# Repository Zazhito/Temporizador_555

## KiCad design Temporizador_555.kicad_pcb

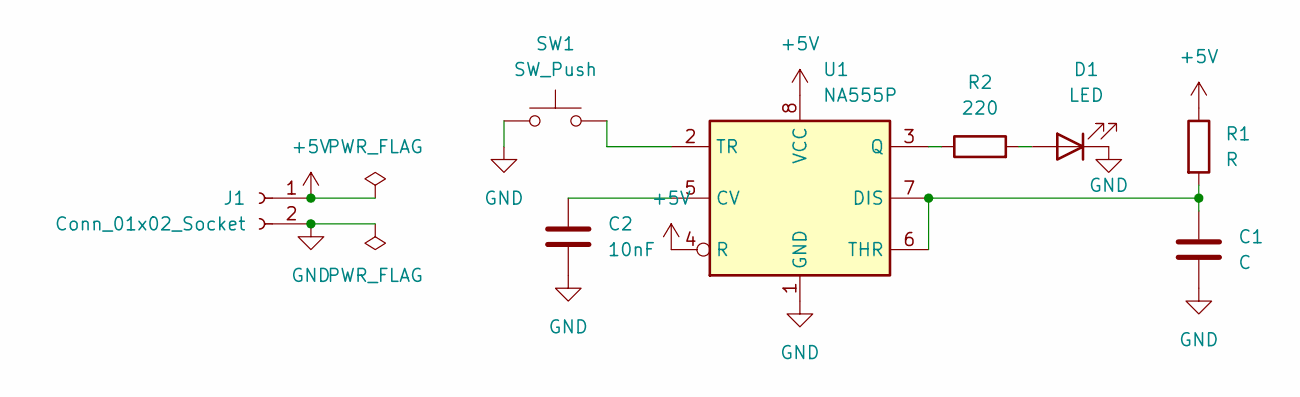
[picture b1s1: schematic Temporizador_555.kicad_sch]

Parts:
C1: C; CP_Radial_D5.0mm_P2.00mm
C2: 10nF; C_Disc_D5.0mm_W2.5mm_P5.00mm
D1: LED; LED_D3.0mm
J1: Conn_01x02_Socket; PinSocket_1x02_P2.54mm_Vertical
R1: R; R_Axial_DIN0207_L6.3mm_D2.5mm_P7.62mm_Horizontal
R2: 220; R_Axial_DIN0207_L6.3mm_D2.5mm_P7.62mm_Horizontal
SW1: SW_Push; SW_PUSH_6mm
U1: NA555P; DIP-8_W7.62mm

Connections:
+5V: J1.1, R1.1, U1.4 (R), U1.8 (VCC)
GND: C1.2, C2.2, D1.1 (K), J1.2, SW1.1, U1.1 (GND)
unnamed: D1.2 (A), R2.2
unnamed: C2.1, U1.5 (CV)
unnamed: C1.1, R1.2, U1.6 (THR), U1.7 (DIS)
unnamed: R2.1, U1.3 (Q)
unnamed: SW1.2, U1.2 (TR)

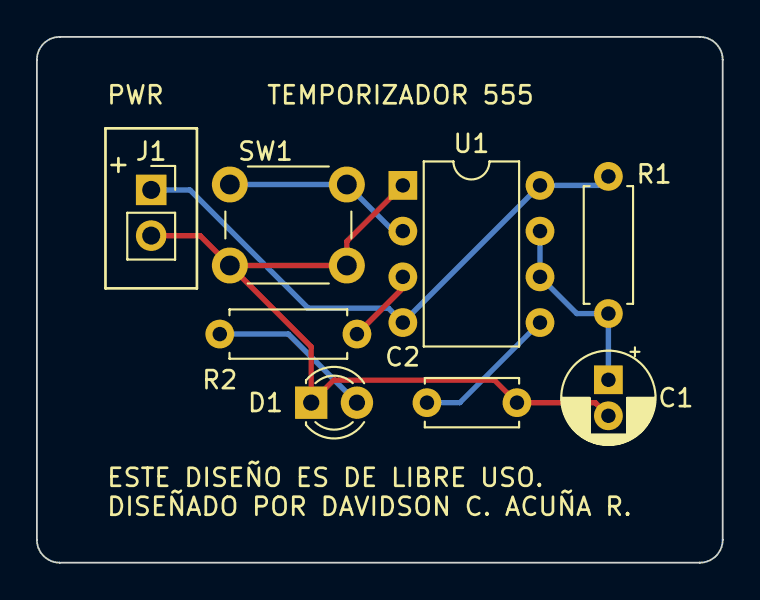
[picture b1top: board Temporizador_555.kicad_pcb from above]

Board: 2 copper layers, 38.1 x 29.2 mm, 8 parts (0 on the bottom side), 7 nets.
